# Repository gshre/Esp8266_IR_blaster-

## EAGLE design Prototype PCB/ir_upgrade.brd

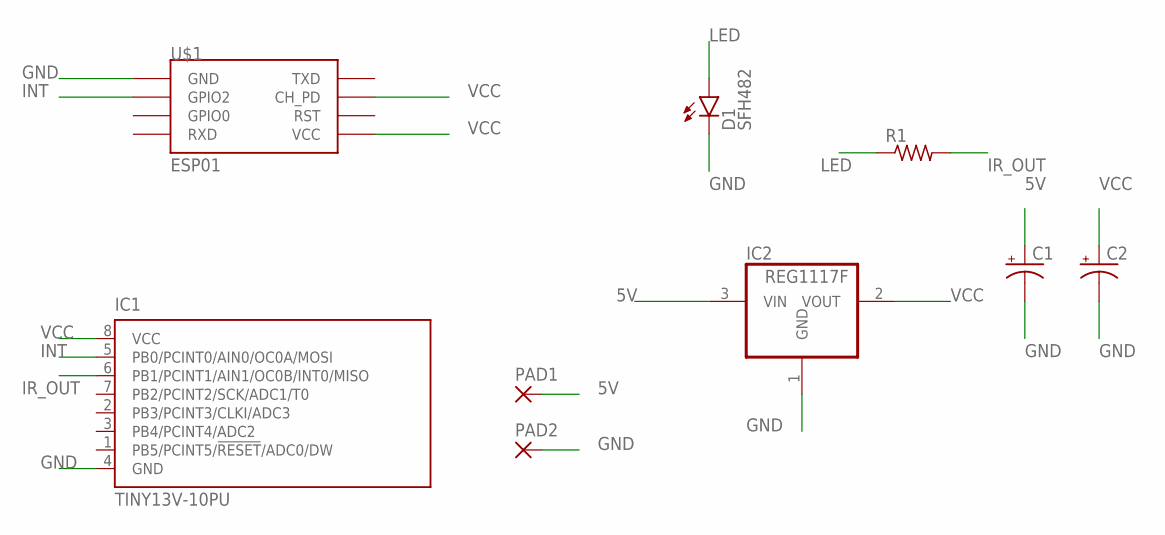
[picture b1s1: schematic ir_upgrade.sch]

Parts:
C1, C2: CPOL-USTT5D7; TT5D7
D1: SFH482
IC1: TINY13V-10PU; DIL08
IC2: REG1117F; DD-3
PAD1, PAD2: 2,15/1,0
R1: R-US_VMTA55; VMTA55
U$1: ESP01

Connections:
5V: C1.+, IC2.3 (VIN), PAD1.1
GND: C1.-, C2.-, D1.K (C), IC1.4 (GND), IC2.1 (GND), PAD2.1, U$1.GND
INT: IC1.5 (PB0/PCINT0/AIN0/OC0A/MOSI), U$1.GPIO2
IR_OUT: IC1.6 (PB1/PCINT1/AIN1/OC0B/INT0/MISO), R1.2
LED: D1.A, R1.1
VCC: C2.+, IC1.8 (VCC), IC2.2 (VOUT), U$1.CH_PD, U$1.VCC

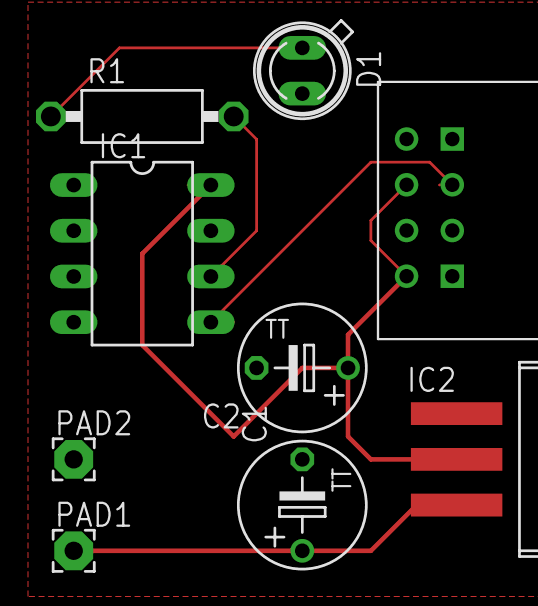
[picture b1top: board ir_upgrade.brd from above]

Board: 2 copper layers, 9 parts (0 on the bottom side), 6 nets.

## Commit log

2020-06-18 added pcb Design
